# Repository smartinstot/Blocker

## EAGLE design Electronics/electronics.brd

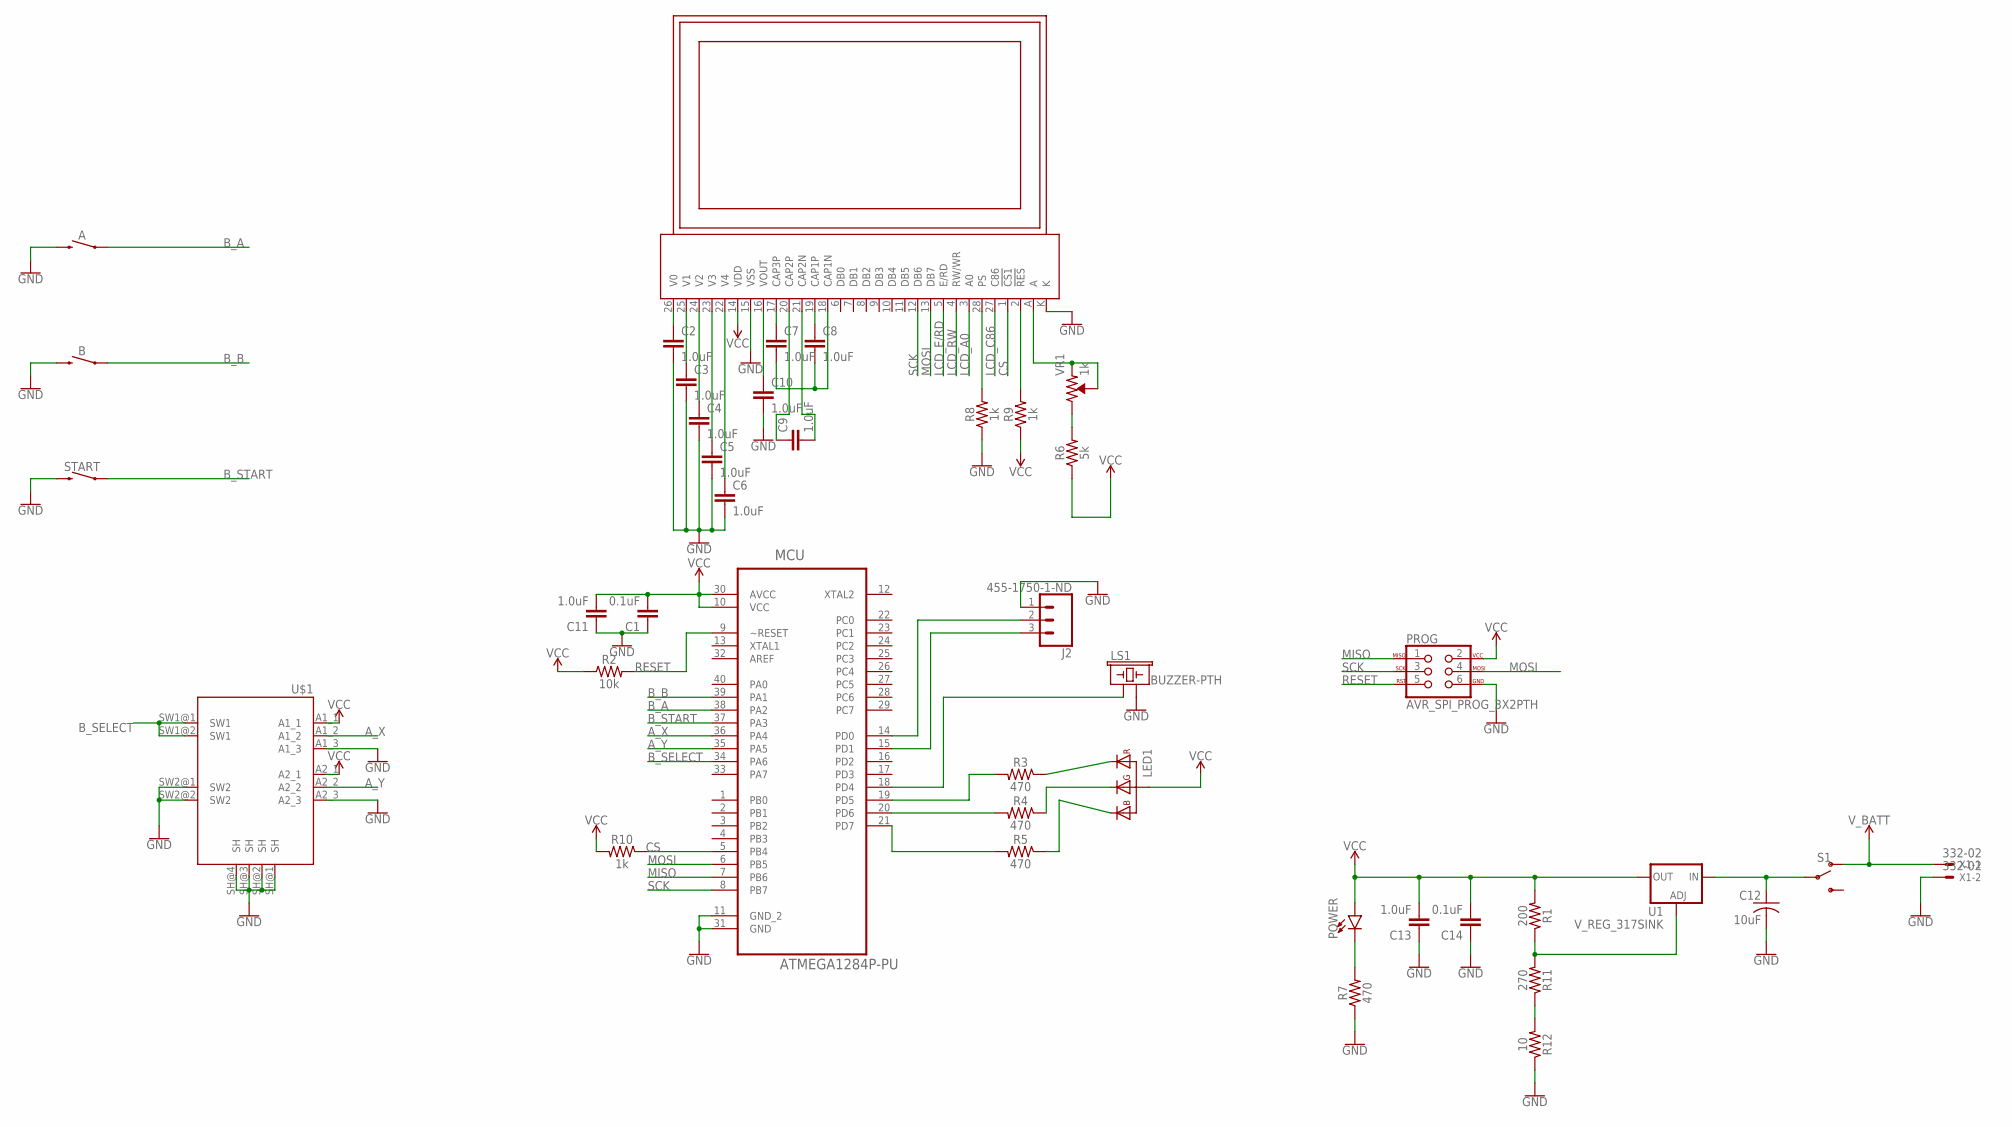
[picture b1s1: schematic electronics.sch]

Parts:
A: MOMENTARY-SWITCH-SPST-PTH-6.0MM; TACTILE_SWITCH_PTH_6.0MM
A1: LCD
B: MOMENTARY-SWITCH-SPST-PTH-6.0MM; TACTILE_SWITCH_PTH_6.0MM
C1, C14: 0.1uF; 0805
C2, C3, C4, C5, C6, C7, C8, C9, C10, C11, C13: 1.0uF; 0805
C12: 10uF; C1206
J2: 455-1750-1-ND; 1X03
LED1: RGB_LED; 5MM_LED
LS1: BUZZER-PTH; BUZZER-12MM
MCU: ATMEGA1284P-PU; DIP254P1524X483-40
POWER: LED5MM; LED_5MM
PROG: AVR_SPI_PROG_3X2PTH; 2X3
R1: 200; AXIAL-0.3
R2: 10k; 0805
R3, R4, R5, R7: 470; 0805
R6: 5k; 0805
R8, R9, R10: 1k; 0805
R11: 270; AXIAL-0.3
R12: 10; AXIAL-0.3
S1: SWITCH-SPDT-PTH-11.6X4.0MM; SWITCH_SPDT_PTH_11.6X4.0MM
START: MOMENTARY-SWITCH-SPST-PTH-6.0MM; TACTILE_SWITCH_PTH_6.0MM
U1: V_REG_317SINK; TO220-ADJ
U$1: JOYSTICK; JOY
VR1: 1k; TRIMPOT-PTH-3386U
X1: 332-02

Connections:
A_X: MCU.36 (PA4), U$1.A1_2
A_Y: MCU.35 (PA5), U$1.A2_2
B_A: A.1, MCU.38 (PA2)
B_B: B.1, MCU.39 (PA1)
B_SELECT: MCU.34 (PA6), U$1.SW1@1 (SW1), U$1.SW1@2 (SW1)
B_START: MCU.37 (PA3), START.1
CS: A1.1 (!CS1), MCU.5 (PB4), R10.1
GND: A.3 (2), A1.15 (VSS), A1.K, B.3 (2), C1.1, C2.2, C3.2, C4.2, C5.2, C6.2, C10.2, C11.1, C12.2, C13.1, C14.1, J2.1, LS1.- (2), MCU.11 (GND_2), MCU.31 (GND), PROG.6, R7.1, R8.1, R12.P$1 (1), START.3 (2), U$1.A1_3, U$1.A2_3, U$1.SH@1 (SH), U$1.SH@2 (SH), U$1.SH@3 (SH), U$1.SH@4 (SH), U$1.SW2@1 (SW2), U$1.SW2@2 (SW2), X1.2
LCD_A0: A1.3 (A0)
LCD_C86: A1.27 (C86)
LCD_E/RD: A1.5 (E/RD)
LCD_RW: A1.4 (RW/WR)
MISO: MCU.7 (PB6), PROG.1
MOSI: A1.13 (DB7), MCU.6 (PB5), PROG.4
unnamed: A1.A, VR1.1 (CCW), VR1.2 (WIPER)
unnamed: MCU.19 (PD5), R3.2
unnamed: LED1.G, R4.1
unnamed: LED1.R, R3.1
unnamed: LED1.B, R5.1
unnamed: R6.2, VR1.3 (CW)
unnamed: MCU.20 (PD6), R4.2
unnamed: POWER.K (C), R7.2
unnamed: A1.26 (V0), C2.1
unnamed: A1.25 (V1), C3.1
unnamed: A1.24 (V2), C4.1
unnamed: A1.23 (V3), C5.1
unnamed: A1.22 (V4), C6.1
unnamed: A1.19 (CAP1P), C8.1
unnamed: A1.17 (CAP3P), C7.1
unnamed: A1.18 (CAP1N), C7.2, C8.2
unnamed: A1.20 (CAP2P), C9.1
unnamed: A1.21 (CAP2N), C9.2
unnamed: A1.16 (VOUT), C10.1
unnamed: A1.28 (PS), R8.2
unnamed: A1.2 (!RES), R9.2
unnamed: MCU.21 (PD7), R5.2
unnamed: LS1.+ (1), MCU.18 (PD4)
unnamed: R11.P$1 (1), R12.P$2 (2)
unnamed: J2.2, MCU.14 (PD0)
unnamed: J2.3, MCU.15 (PD1)
unnamed: C12.1, S1.2, U1.IN
unnamed: R1.P$1 (1), R11.P$2 (2), U1.ADJ
RESET: MCU.9 (~RESET), PROG.5, R2.2
SCK: A1.12 (DB6), MCU.8 (PB7), PROG.3
VCC: A1.14 (VDD), C1.2, C11.2, C13.2, C14.2, LED1.C (A), MCU.10 (VCC), MCU.30 (AVCC), POWER.A, PROG.2, R1.P$2 (2), R2.1, R6.1, R9.1, R10.2, U1.OUT, U$1.A1_1, U$1.A2_1
V_BATT: S1.1 (O), X1.1

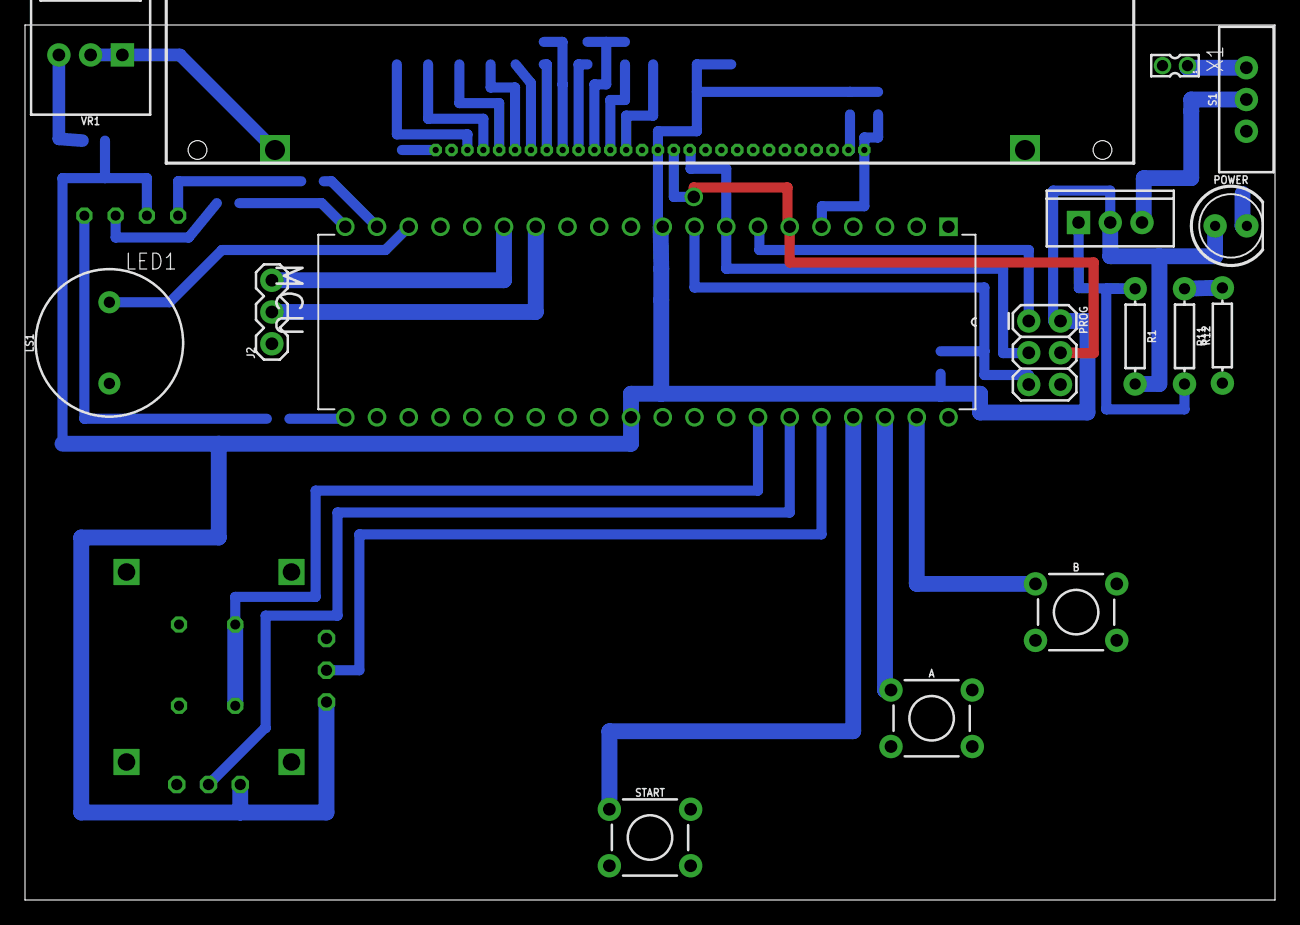
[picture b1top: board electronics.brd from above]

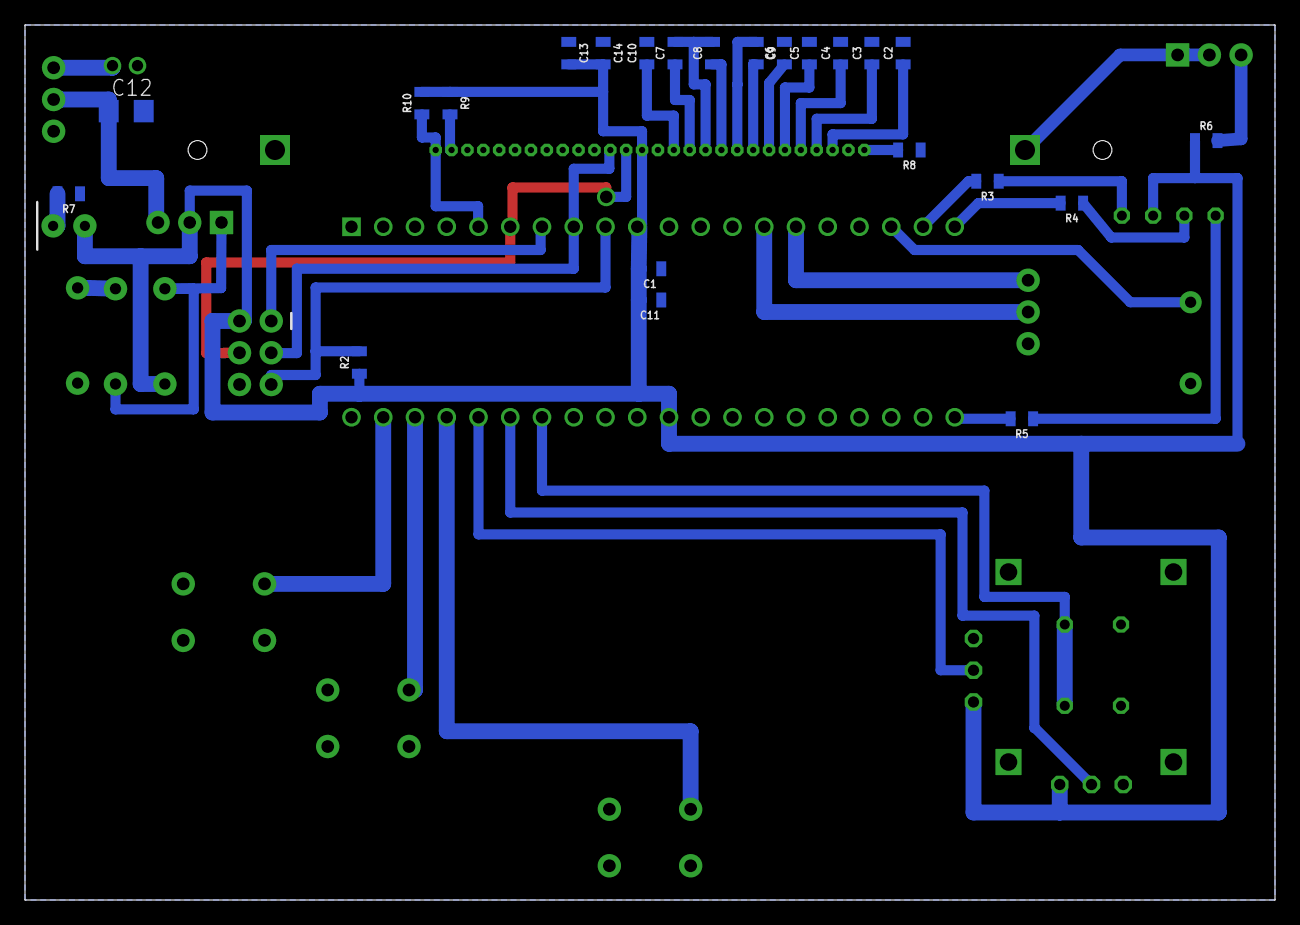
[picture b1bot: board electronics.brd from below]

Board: 2 copper layers, 100.0 x 70.0 mm, 41 parts (23 on the bottom side), 42 nets.

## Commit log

2017-12-02 Added basic initalization code
2017-12-02 Added datasheets
2017-12-02 Created Eagle project and added relevent libs
2017-12-02 Made lcd lib compile
2017-12-02 Added LCD library
2017-12-02 Regulator datasheet
2017-12-02 Added a snake program
2017-12-02 Finished Schematic
2017-12-02 Finished PCB routing
2017-12-02 Added changes

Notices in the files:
parts and their libraries:
SparkFun-Connectors: Licensing: Creative Commons ShareAlike 4.0 International - https://creativecommons.org/licenses/by-sa/4.0
